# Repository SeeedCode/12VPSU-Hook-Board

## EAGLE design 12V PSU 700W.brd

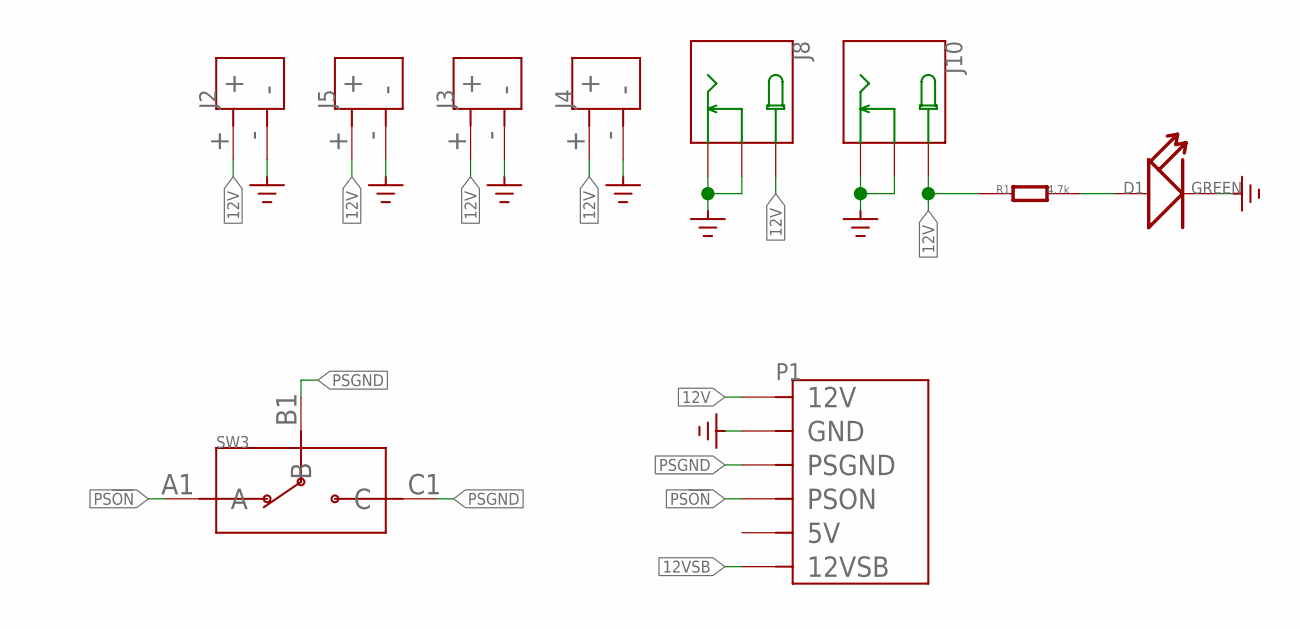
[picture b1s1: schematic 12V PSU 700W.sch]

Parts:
D1: GREEN; LED-0603
J2, J5: XT-PWR-CONN-THXT60-F; XT60-F-TH
J3, J4: XT-PWR-CONN-THXT30-F; XT30-F-TH
J8, J10: POWER-JACK-DC'DC-012A'; DCJ3P-14.2X11.0X9.0MM-V
P1: PSU-750W
R1: 4.7k; R0603
SW3: SWITCH-STICK-3P

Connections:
12V: J2.+, J3.+, J4.+, J5.+, J8.+, J10.+, P1.P4 (12V), P1.P5 (12V), P1.P6 (12V), R1.1
12VSB: P1.7 (12VSB)
GND: D1.-, J2.-, J3.-, J4.-, J5.-, J8.-, J8.S (CDN), J10.-, J10.S (CDN), P1.P1 (GND), P1.P2 (GND), P1.P3 (GND)
unnamed: D1.+, R1.2
PS!ON: P1.11 (PSON), SW3.A1 (A)
PSGND: P1.15 (PSGND), SW3.B1 (B), SW3.C1 (C)

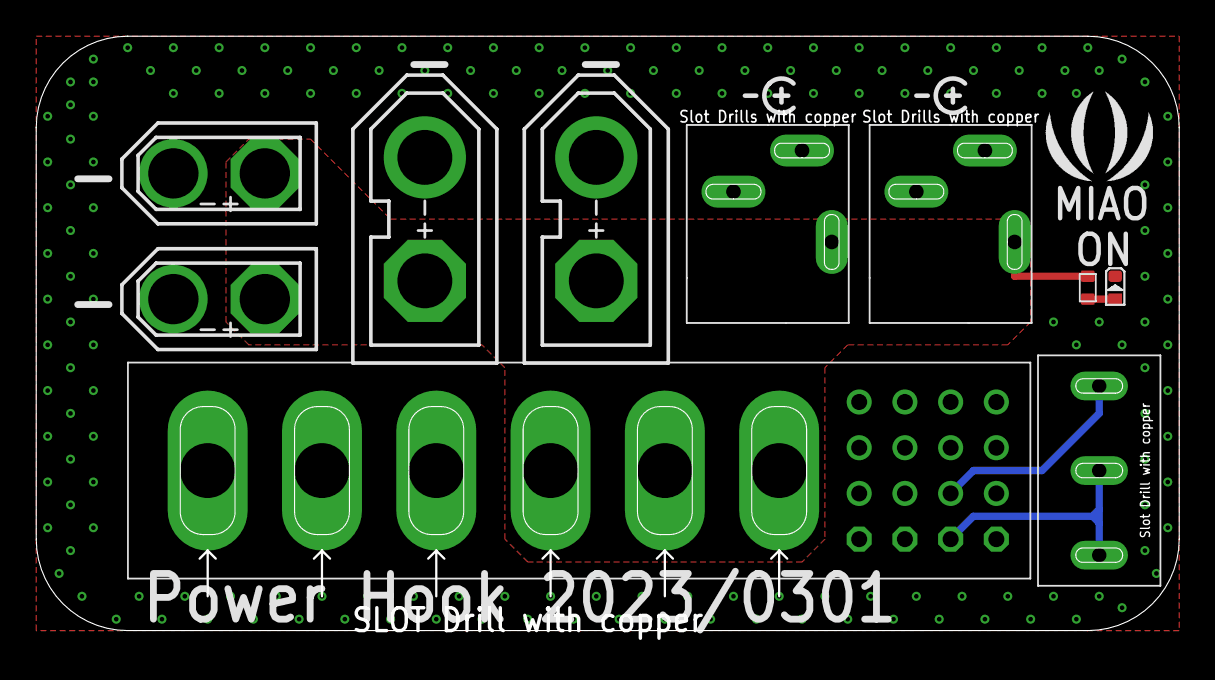
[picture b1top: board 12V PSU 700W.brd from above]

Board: 4 copper layers, 63.4 x 33.7 mm, 11 parts (0 on the bottom side), 5 nets.

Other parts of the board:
U$11: SEEED-SILK-280*268MIL
